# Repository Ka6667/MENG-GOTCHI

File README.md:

# MENG-GOTCHI

## Table of Content
* [What is MENG-GOTCHI](#what-is-meng-gotchi)
* [Why did I build it](#why-did-i-build-it)
* [How to use MENG-GOTCHI](#how-to-use-meng-gotchi)
* [Schematics](#schematics)
* [PCB Design](#pcb-design)
* [3D MODEL](#3d-model)
## What is MENG-GOTCHI
MENG-GOTCHI is my custom digital pet. my custom Tamagotchi-style bunny! She’s super smart and teaches you new English words every day. The catch? You gotta keep her fed, play with her, and sometimes give her some love through the touch sensor when she asks.

## Why did I build it
I have a friend who teaches me Chinese. She once told me about a dog she used to own, but her family had to give it away. She has always wanted another pet, but her family refuses, so I decided to build one for her! She also works as an English tutor and is currently preparing for an exam that requires her to memorize complex vocabulary. To help her out, I added a feature to the pet to help her practice the 45 words she always forgets!

## How to use MENG-GOTCHI
It's incredibly simple to use! There are three push buttons: the left button feeds the pet, the middle button plays with her, and the right button puts her to sleep. If you long-press the left button, it activates study mode and reviews five English words with you. It even has a touch sensor so you can actually pet the MENG bunny. I am sure she is going to love it!
## Schematics

## PCB Design

## 3D MODEL

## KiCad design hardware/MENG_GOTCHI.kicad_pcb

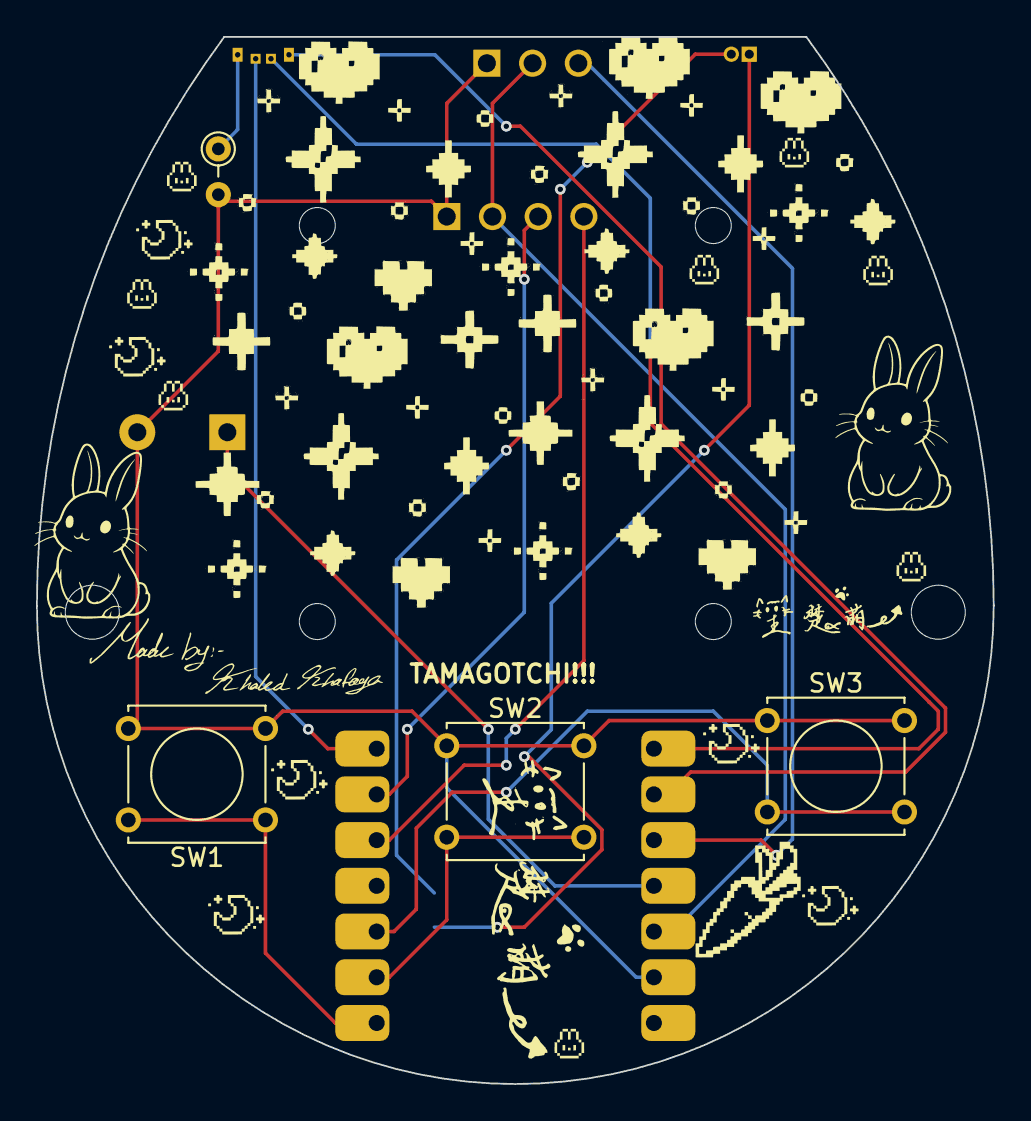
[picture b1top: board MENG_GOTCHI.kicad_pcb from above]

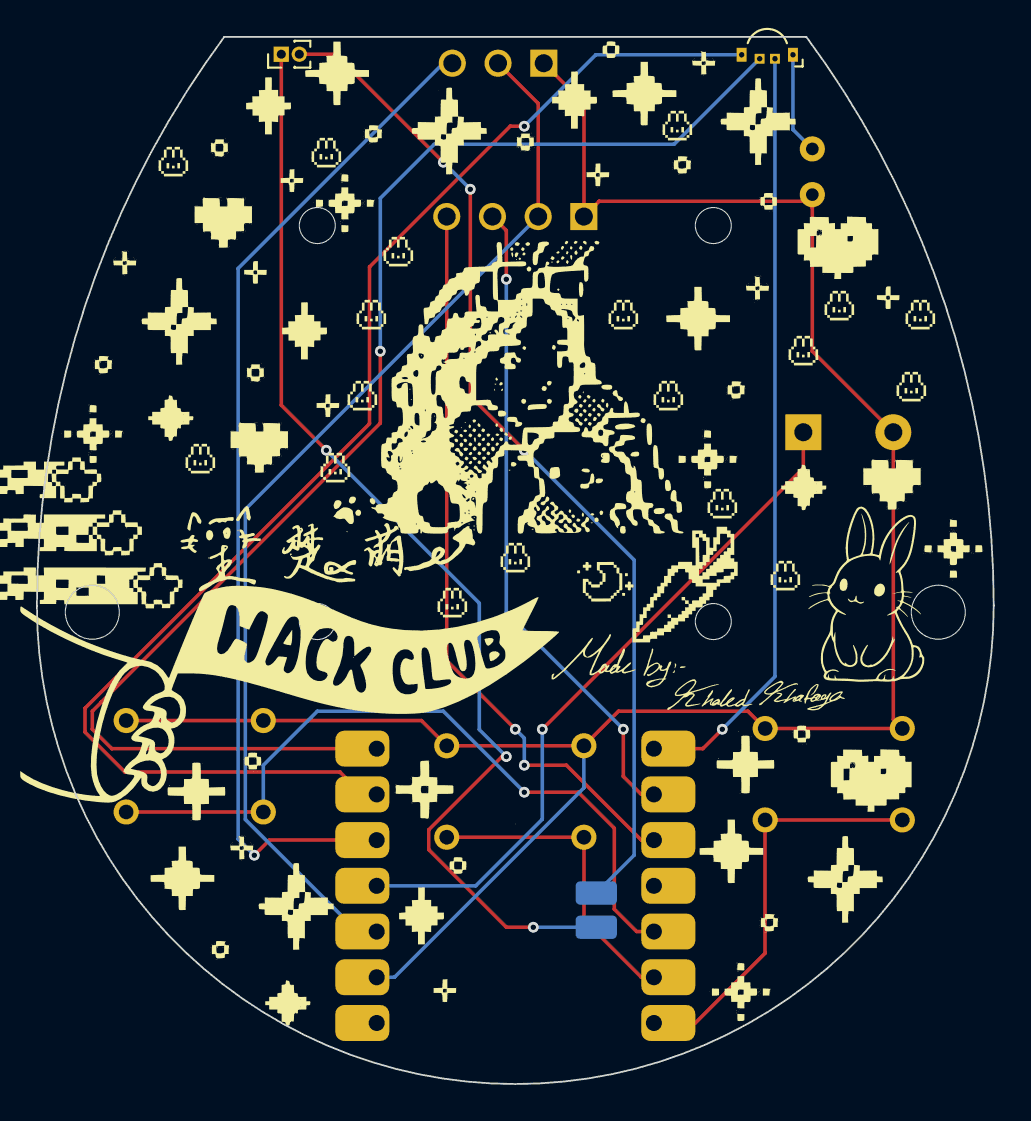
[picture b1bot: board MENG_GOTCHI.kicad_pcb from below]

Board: 2 copper layers, 53.2 x 58.2 mm, 9 parts (3 on the bottom side), 13 nets.

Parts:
BZ1: Buzzer; Buzzer_TDK_PS1240P02BT_D12.2mm_H6.5mm
D1: Red LED; LED_RGB_Everlight_EASV3015RGBA0_Horizontal
R1: 330R; R_Axial_DIN0204_L3.6mm_D1.6mm_P2.54mm_Vertical
SW1, SW2, SW3: SW_Push; SW_Tactile_Straight_KSA0Axx1LFTR
U3: XIAO-ESP32-C6-SMD; MCU_Seeed_ESP32C3
U4: DM-OLED096-636; MODULE_DM-OLED096-636
U6: TTP223B-Touch-Sensor; TTP223B

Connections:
-VSW: U3.12 (3V3), U3.14 (5V), U4.2 (VCC_IN), U6.2 (VCC)
GND: BZ1.2 (-), R1.2, SW1.2, SW2.1, SW3.1, U3.13 (GND), U4.1 (GND), U6.1 (GND)
unnamed: BZ1.1 (+), U3.11 (GPIO18_D10_MOSI)
unnamed: D1.2 (A), U3.7 (GPIO16_D6_TX)
unnamed: D1.1 (K), R1.1
unnamed: D1.3, U3.8 (GPIO17_D7_RX)
unnamed: D1.4, U3.9 (GPIO19_D8_SCK)
unnamed: SW1.1, U3.1 (GPIO0_A0_D0)
unnamed: SW2.2, U3.2 (GPIO1_A1_D1)
unnamed: SW3.2, U3.3 (GPIO2_A2_D2)
unnamed: U3.10 (GPIO20_D9_MISO), U6.3
unnamed: U3.5 (GPIO22_D4_SDA), U4.4 (SDA)
unnamed: U3.6 (GPIO23_D5_SCL), U4.3 (SCL)

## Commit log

2026-06-08 README.md
2026-06-08 Create Hardware
2026-06-08 Rename MENG-GOTCHI.pdf to ZINE (MENG-GOTCHI).pdf
2026-06-08 Create tem
2026-06-08 Create temp
